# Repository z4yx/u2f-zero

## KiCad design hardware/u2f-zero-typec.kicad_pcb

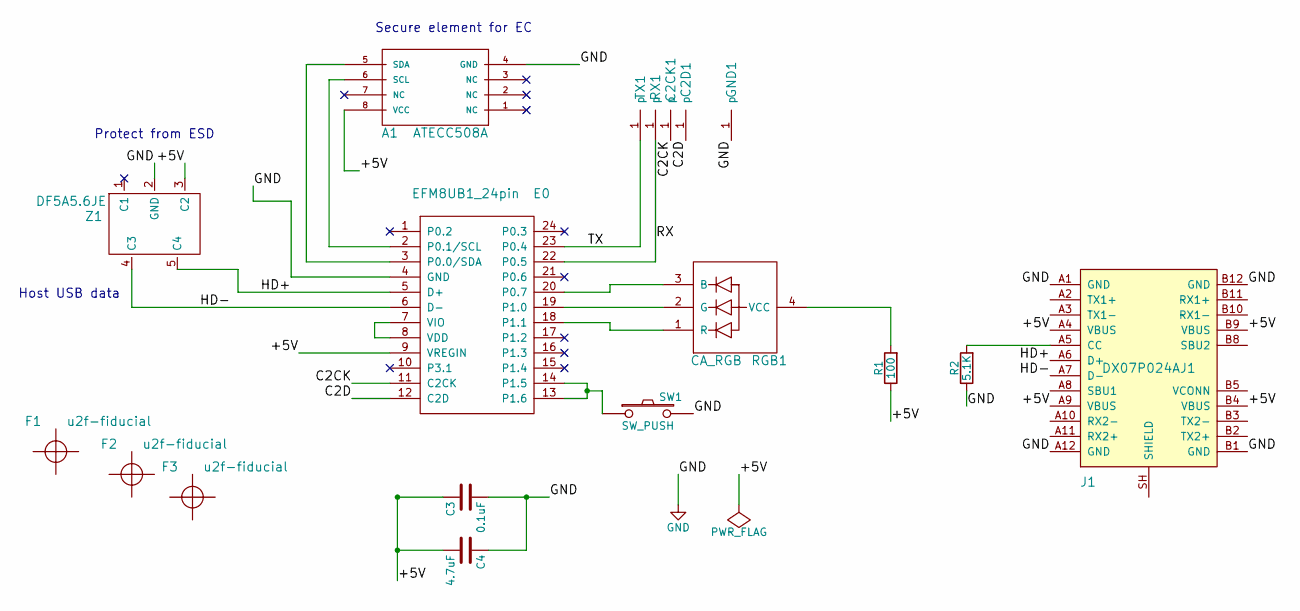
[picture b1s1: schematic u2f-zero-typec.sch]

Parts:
A1: ATECC508A; SOIC-8_3.9x4.9mm_Pitch1.27mm; MFG Part Num ATECC508A-SSHDA-B
C2CK1, C2D1: debug-pin; debug
C3: 0.1uF; C_0402; MFG Part Num CL05A104MP5NNNC
C4: 4.7uF; C_0603; MFG Part Num CL10B475KQ8NQNC
E0: EFM8UB1_24pin; QSOP-24_3.9x8.7mm_Pitch0.635mm_fat; MFG Part Num EFM8UB11F16G-C-QSOP24
F1, F2, F3: u2f-fiducial
GND1: debug-pin; debug
J1: DX07P024AJ1; USB-TypeC-Male
R1: 100; R_0603; MFG Part Num CRCW0603100RFKEA
R2: 5.1K; R_0603
RGB1: CA_RGB; LED-0606; MFG Part Num LTST-C19HE1WT
RX1: debug-pin; debug
SW1: SW_PUSH; u2f-button; MFG Part Num TL3305AF260QG
TX1: debug-pin; debug
Z1: DF5A5.6JE; SOT-553; MFG Part Num DF5A5.6JE,LM

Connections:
/+5V: A1.8 (VCC), C3.1, C4.2, E0.9 (VREGIN), J1.A4 (VBUS), J1.A9 (VBUS), J1.B4 (VBUS), J1.B9 (VBUS), R1.1, Z1.3 (C2)
/C2CK: C2CK1.1, E0.11 (C2CK)
/C2D: C2D1.1, E0.12 (C2D)
/HD+: E0.5 (D+), J1.A6 (D+), Z1.5 (C4)
/HD-: E0.6 (D-), J1.A7 (D-), Z1.4 (C3)
/RX: E0.22 (P0.5), RX1.1
/TX: E0.23 (P0.4), TX1.1
GND: A1.4 (GND), C3.2, C4.1, E0.4 (GND), GND1.1, J1.A1 (GND), J1.A12 (GND), J1.B1 (GND), J1.B12 (GND), R2.1, SW1.2, Z1.2 (GND)
unnamed: A1.5 (SDA), E0.3 (P0.0/SDA)
unnamed: A1.6 (SCL), E0.2 (P0.1/SCL)
unnamed: E0.7 (VIO), E0.8 (VDD)
unnamed: E0.13 (P1.6), E0.14 (P1.5), SW1.1
unnamed: E0.18 (P1.1), RGB1.1 (R)
unnamed: E0.19 (P1.0), RGB1.2 (G)
unnamed: E0.20 (P0.7), RGB1.3 (B)
unnamed: J1.A5 (CC), R2.2
unnamed: R1.2, RGB1.4 (VCC)

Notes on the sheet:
Protect from ESD
Host USB data
Secure element for EC

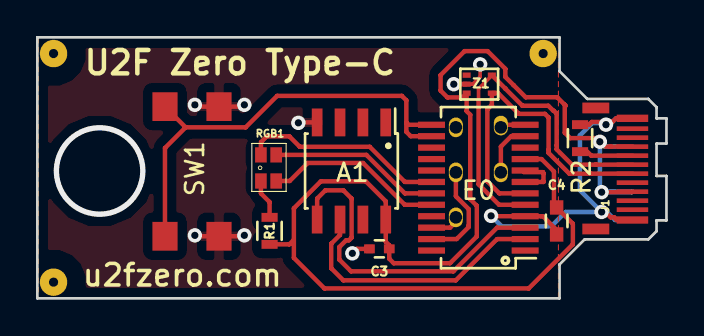
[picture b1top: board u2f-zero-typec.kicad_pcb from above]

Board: 2 copper layers, 35.0 x 14.5 mm, 18 parts (0 on the bottom side), 17 nets.

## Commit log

2017-02-02 stm32f042 based design
2017-02-03 add USB TypeC connector
2017-02-03 PCB layout of type-c version
2017-02-03 add connector models
2017-02-04 fix wrong common pin position of LED
2017-02-08 STM32 project
2017-02-08 porting some code
2017-02-08 fix ifdef directive
2017-02-08 USB related code ported
2017-02-08 touch sensor support
2017-02-25 update component parameters
2017-03-07 fix UART printing
2017-03-11 upgrade CubeMX, “jumping to bootloader” test
2017-03-11 enable special command for upgrading
2017-03-13 touch sensor tuning
2017-03-13 fix PWM control
2017-03-16 type of va_arg promoted to 'int'
2017-03-16 USB VID/PID update
2017-03-17 fix endian and memory alignment issues
2017-03-17 code to jump into bootloader
2017-03-18 support for U2F_CONFIG_BOOTLOADER
2017-03-19 U2F_CONFIG_BOOTLOADER is only allowed in configuration firmware
2017-03-19 do not hang when receiving invalid commands (to pass U2F tests)
2017-03-19 c99 std
2017-03-22 release build settings
2017-03-22 bug fix: inverted touch button state
2017-03-22 fix uninitialized local variable
2017-03-22 another byte order problem fix
2017-03-22 waiting for USB idle state
2017-03-23 debug messages
2017-03-23 update manufacture
2017-03-23 optimize for response time
2017-03-23 update setup script
2017-03-23 build USB serial number based on unique chip ID
